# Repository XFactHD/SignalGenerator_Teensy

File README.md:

# SignalGenerator_Teensy
 Teensy 4.0 based 1MSPS Signal Generator

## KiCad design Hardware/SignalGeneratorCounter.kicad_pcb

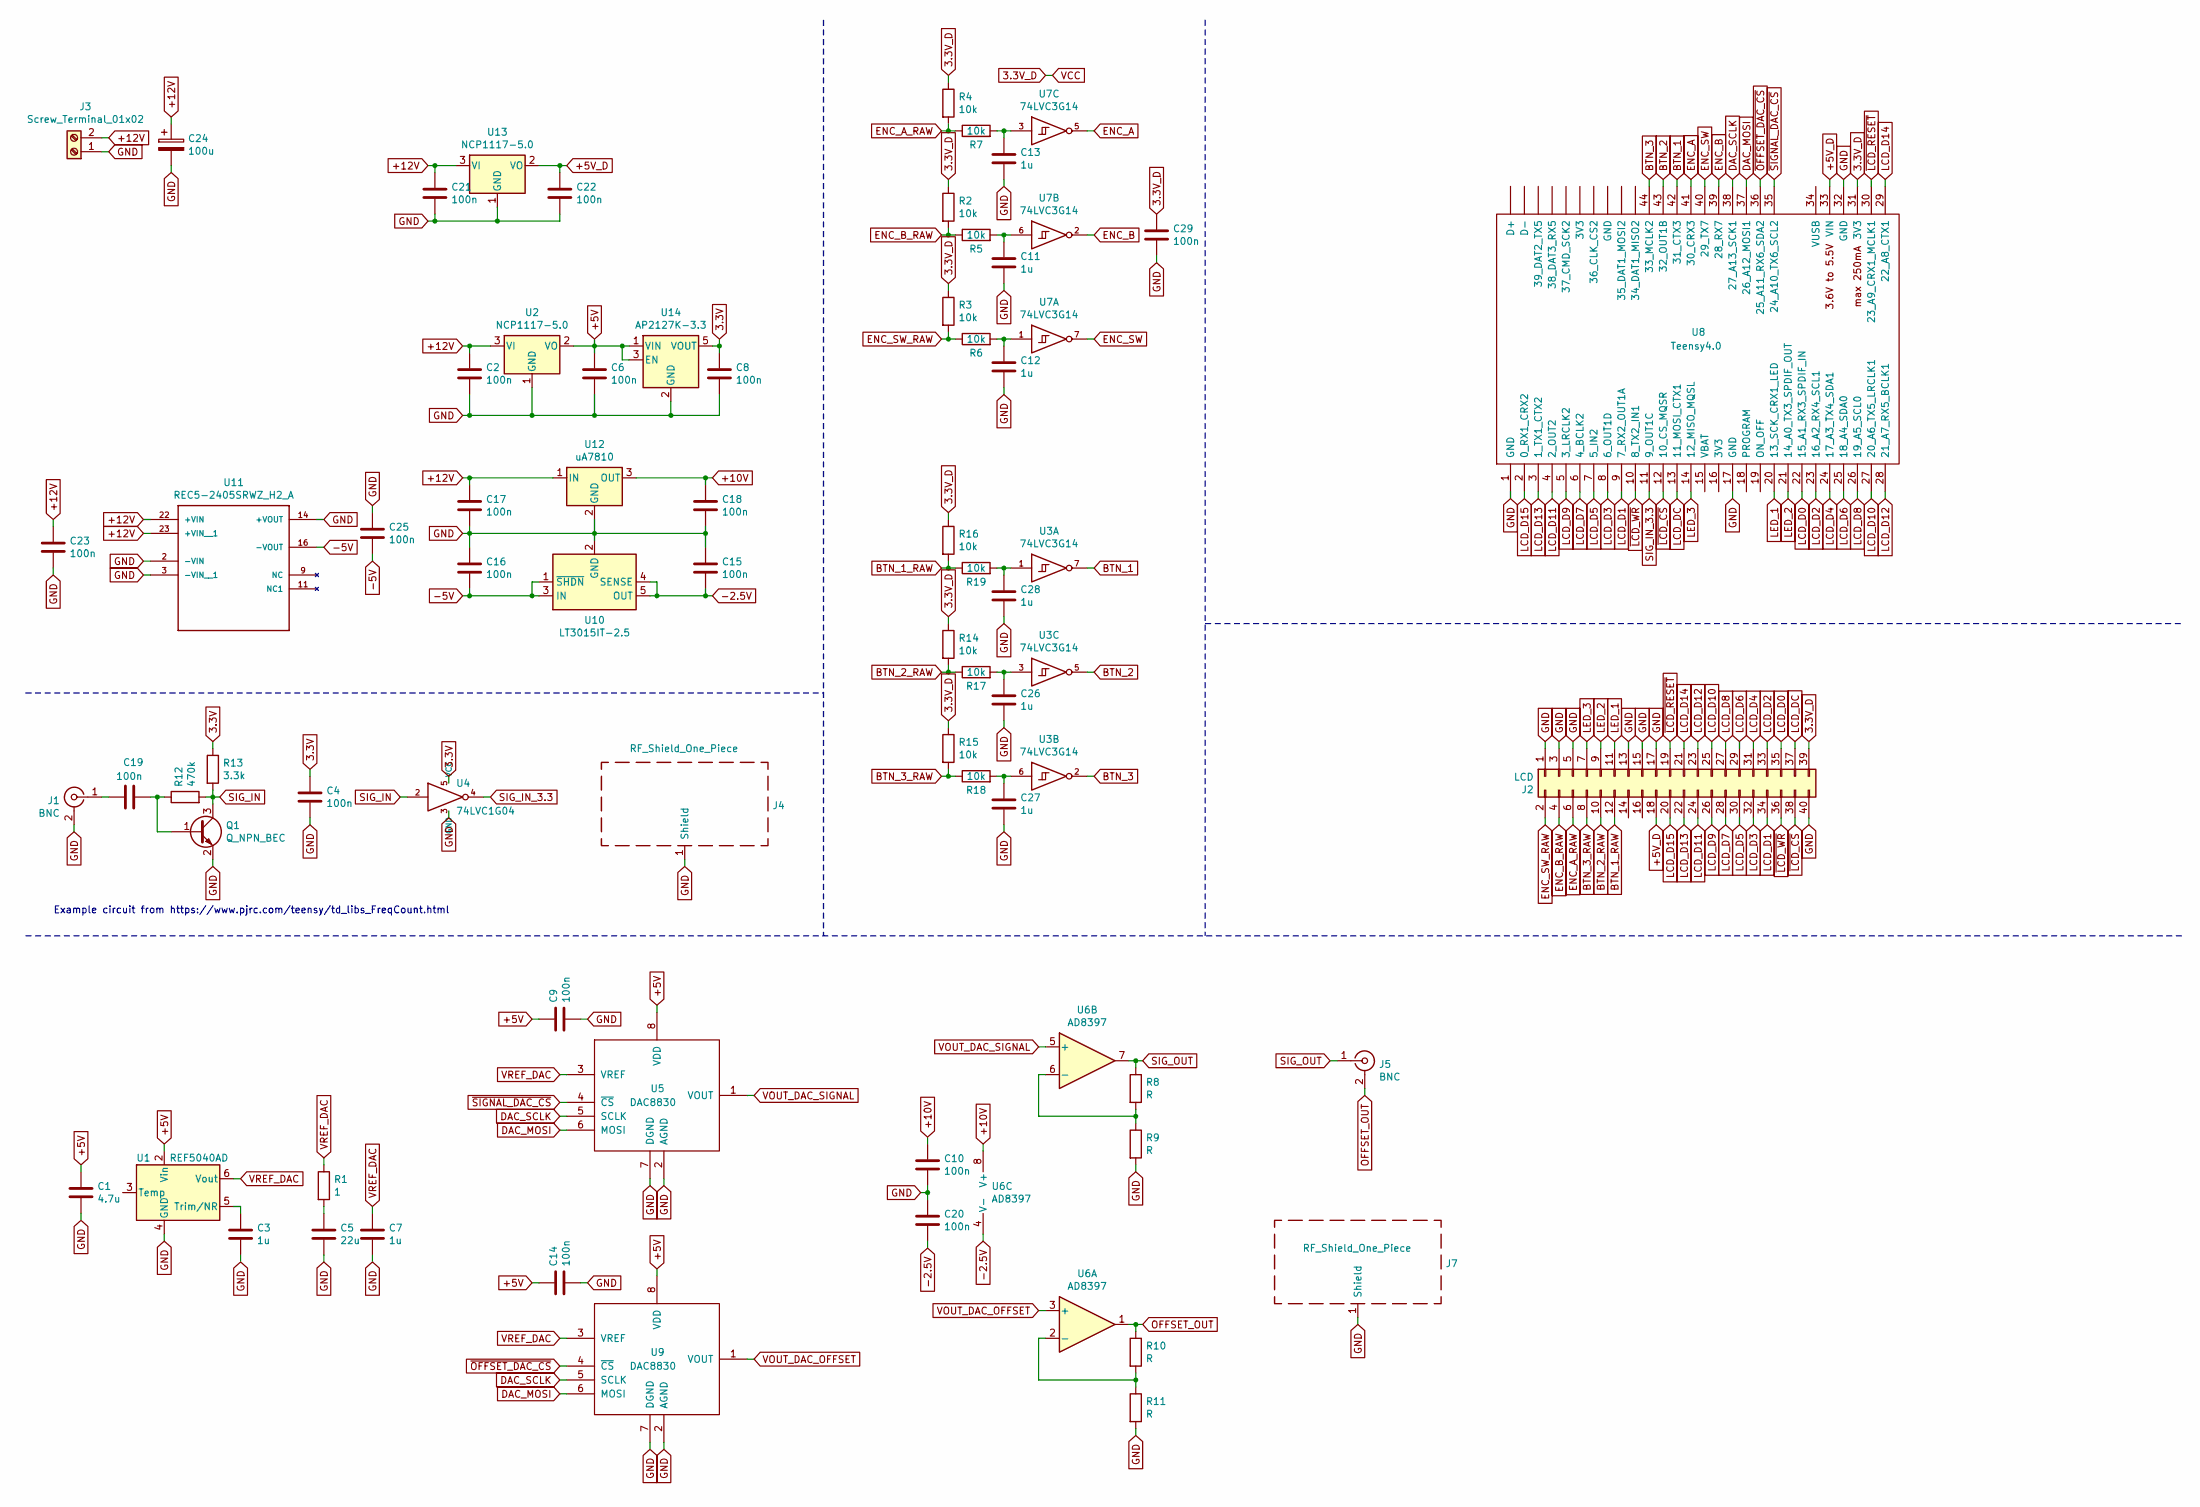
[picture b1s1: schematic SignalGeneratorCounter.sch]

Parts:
C1: 4.7u; C_0805
C2, C4, C6, C8, C9, C10, C14, C15, C16, C17, C18, C19, C20, C21, C22, C23, C25, C29: 100n; C_0805
C3, C7, C11, C12, C13, C26, C27, C28: 1u; C_0805
C5: 22u; C_0805
C24: 100u; CP_Tantalum_Case-C_EIA-6032-28_Reflow
J1, J5: BNC; BNC_Socket_TYCO-AMP
J2: LCD; HARTING_15210402601000
J3: Screw_Terminal_01x02; PhoenixContact_MSTBVA-G_02x5.08mm_Vertical
J4: RF_Shield_One_Piece; Laird_Technologies_BMI-S-201-F_13.66x12.70mm
J7: RF_Shield_One_Piece; Laird_Technologies_BMI-S-209-F_29.36x18.50mm
Q1: Q_NPN_BEC; SOT-23
R1: 1; R_0805
R2, R3, R4, R5, R6, R7, R14, R15, R16, R17, R18, R19: 10k; R_0805
R8, R9, R10, R11: R; R_0805
R12: 470k; R_0805
R13: 3.3k; R_0805
U1: REF5040AD; SOIC-8_3.9x4.9mm_Pitch1.27mm
U2, U13: NCP1117-5.0; TO-252-2
U3, U7: 74LVC3G14; VSSOP-8_2.4x2.1mm_Pitch0.5mm
U4: 74LVC1G04; SOT-23-5
U5, U9: DAC8830; SOIC-8_3.9x4.9mm_Pitch1.27mm
U6: AD8397; SOIC-8-1EP_3.9x4.9mm_Pitch1.27mm
U8: Teensy4.0; Teensy40_WithSMT_NoBack_No34
U10: LT3015IT-2.5; TO-263-5_TabPin3
U11: REC5-2405SRWZ_H2_A
U12: uA7810; TO-263-3_TabPin2
U14: AP2127K-3.3; SOT-23-5

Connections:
3.3V: C4.1, C8.1, R13.1, U4.5 (VCC), U14.5 (VOUT)
3.3V_D: C29.1, J2.39, R2.1, R3.1, R4.1, R14.1, R15.1, R16.1, U3.8 (VCC), U7.8 (VCC), U8.31 (3V3)
+5V: C1.1, C6.1, C9.1, C14.1, U1.2 (Vin), U2.2 (VO), U5.8 (VDD), U9.8 (VDD), U14.1 (VIN), U14.3 (EN)
+5V_D: C22.1, J2.18, U8.33 (VIN), U13.2 (VO)
+10V: C10.1, C18.1, U6.8 (V+), U12.3 (OUT)
+12V: C2.1, C17.1, C21.1, C23.1, C24.1, J3.2, U2.3 (VI), U11.22 (+VIN), U11.23 (+VIN__1), U12.1 (IN), U13.3 (VI)
-2.5V: C15.2, C20.2, U6.4 (V-), U10.4 (SENSE), U10.5 (OUT)
-5V: C16.2, C25.2, U10.1 (~SHDN), U10.3 (IN), U11.16 (-VOUT)
BTN_1: U3.7, U8.42 (31_CTX3)
BTN_1_RAW: J2.12, R16.2, R19.1
BTN_2: U3.5, U8.43 (32_OUT1B)
BTN_2_RAW: J2.10, R14.2, R17.1
BTN_3: U3.2, U8.44 (33_MCLK2)
BTN_3_RAW: J2.8, R15.2, R18.1
DAC_MOSI: U5.6 (MOSI), U8.37 (26_A12_MOSI1), U9.6 (MOSI)
DAC_SCLK: U5.5 (SCLK), U8.38 (27_A13_SCK1), U9.5 (SCLK)
ENC_A: U7.5, U8.41 (30_CRX3)
ENC_A_RAW: J2.6, R4.2, R7.1
ENC_B: U7.2, U8.39 (28_RX7)
ENC_B_RAW: J2.4, R2.2, R5.1
ENC_SW: U7.7, U8.40 (29_TX7)
ENC_SW_RAW: J2.2, R3.2, R6.1
GND: C1.2, C2.2, C3.2, C4.2, C5.2, C6.2, C7.2, C8.2, C9.2, C10.2, C11.2, C12.2, C13.2, C14.2, C15.1, C16.1, C17.2, C18.2, C20.1, C21.2, C22.2, C23.2, C24.2, C25.1, C26.2, C27.2, C28.2, C29.2, J1.2 (Ext), J2.1, J2.3, J2.5, J2.13, J2.15, J2.17, J2.40, J3.1, J4.1, J7.1, Q1.2 (E), R9.2, R11.2, U1.4 (GND), U2.1 (GND), U3.4 (GND), U4.3 (GND), U5.2 (AGND), U5.7 (DGND), U7.4 (GND), U8.1 (GND), U8.17 (GND), U8.32 (GND), U9.2 (AGND), U9.7 (DGND), U10.2 (GND), U11.2 (-VIN), U11.3 (-VIN__1), U11.14 (+VOUT), U12.2 (GND), U13.1 (GND), U14.2 (GND)
LCD_D0: J2.35, U8.22 (15_A1_RX3_SPDIF_IN)
LCD_D1: J2.34, U8.9 (7_RX2_OUT1A)
LCD_D2: J2.33, U8.23 (16_A2_RX4_SCL1)
LCD_D3: J2.32, U8.8 (6_OUT1D)
LCD_D4: J2.31, U8.24 (17_A3_TX4_SDA1)
LCD_D5: J2.30, U8.7 (5_IN2)
LCD_D6: J2.29, U8.25 (18_A4_SDA0)
LCD_D7: J2.28, U8.6 (4_BCLK2)
LCD_D8: J2.27, U8.26 (19_A5_SCL0)
LCD_D9: J2.26, U8.5 (3_LRCLK2)
LCD_D10: J2.25, U8.27 (20_A6_TX5_LRCLK1)
LCD_D11: J2.24, U8.4 (2_OUT2)
LCD_D12: J2.23, U8.28 (21_A7_RX5_BCLK1)
LCD_D13: J2.22, U8.3 (1_TX1_CTX2)
LCD_D14: J2.21, U8.29 (22_A8_CTX1)
LCD_D15: J2.20, U8.2 (0_RX1_CRX2)
LCD_DC: J2.37, U8.13 (11_MOSI_CTX1)
LED_1: J2.11, U8.20 (13_SCK_CRX1_LED)
LED_2: J2.9, U8.21 (14_A0_TX3_SPDIF_OUT)
LED_3: J2.7, U8.14 (12_MISO_MQSL)
unnamed: C3.1, U1.5 (Trim/NR)
unnamed: C5.1, R1.2
unnamed: C11.1, R5.2, U7.6
unnamed: C12.1, R6.2, U7.1
unnamed: C13.1, R7.2, U7.3
unnamed: C19.1, Q1.1 (B), R12.1
unnamed: C19.2, J1.1 (In)
unnamed: C26.1, R17.2, U3.3
unnamed: C27.1, R18.2, U3.6
unnamed: C28.1, R19.2, U3.1
unnamed: R8.2, R9.1, U6.6 (-)
unnamed: R10.2, R11.1, U6.2 (-)
OFFSET_OUT: J5.2 (Ext), R10.1, U6.1
SIG_IN: Q1.3 (C), R12.2, R13.2, U4.2
SIG_IN_3.3: U4.4, U8.11 (9_OUT1C)
SIG_OUT: J5.1 (In), R8.1, U6.7
VOUT_DAC_OFFSET: U6.3 (+), U9.1 (VOUT)
VOUT_DAC_SIGNAL: U5.1 (VOUT), U6.5 (+)
VREF_DAC: C7.1, R1.1, U1.6 (Vout), U5.3 (VREF), U9.3 (VREF)
~LCD_CS: J2.38, U8.12 (10_CS_MQSR)
~LCD_RESET: J2.19, U8.30 (23_A9_CRX1_MCLK1)
~LCD_WR: J2.36, U8.10 (8_TX2_IN1)
~OFFSET_DAC_CS: U8.36 (25_A11_RX6_SDA2), U9.4 (~CS)
~SIGNAL_DAC_CS: U5.4 (~CS), U8.35 (24_A10_TX6_SCL2)

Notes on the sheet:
Example circuit from https://www.pjrc.com/teensy/td_libs_FreqCount.html

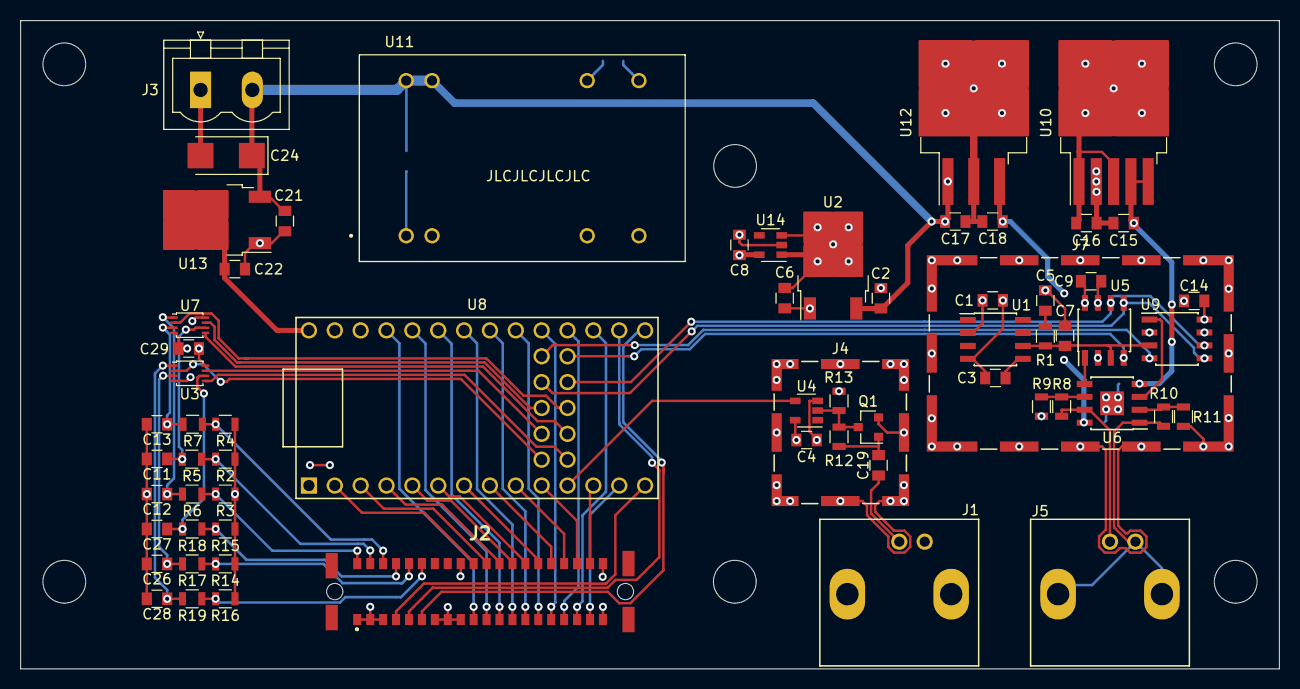
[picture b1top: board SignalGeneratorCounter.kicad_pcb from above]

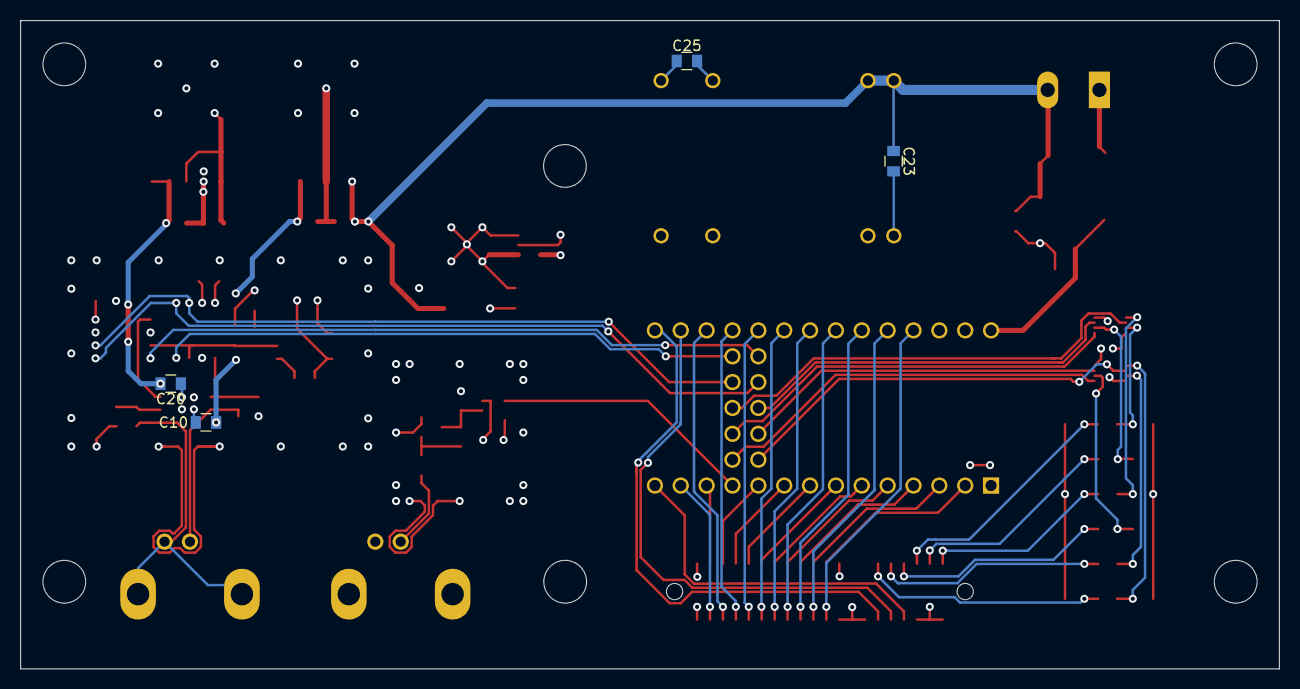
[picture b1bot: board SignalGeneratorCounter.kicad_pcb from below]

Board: 4 copper layers, 123.6 x 63.7 mm, 69 parts (4 on the bottom side), 67 nets.

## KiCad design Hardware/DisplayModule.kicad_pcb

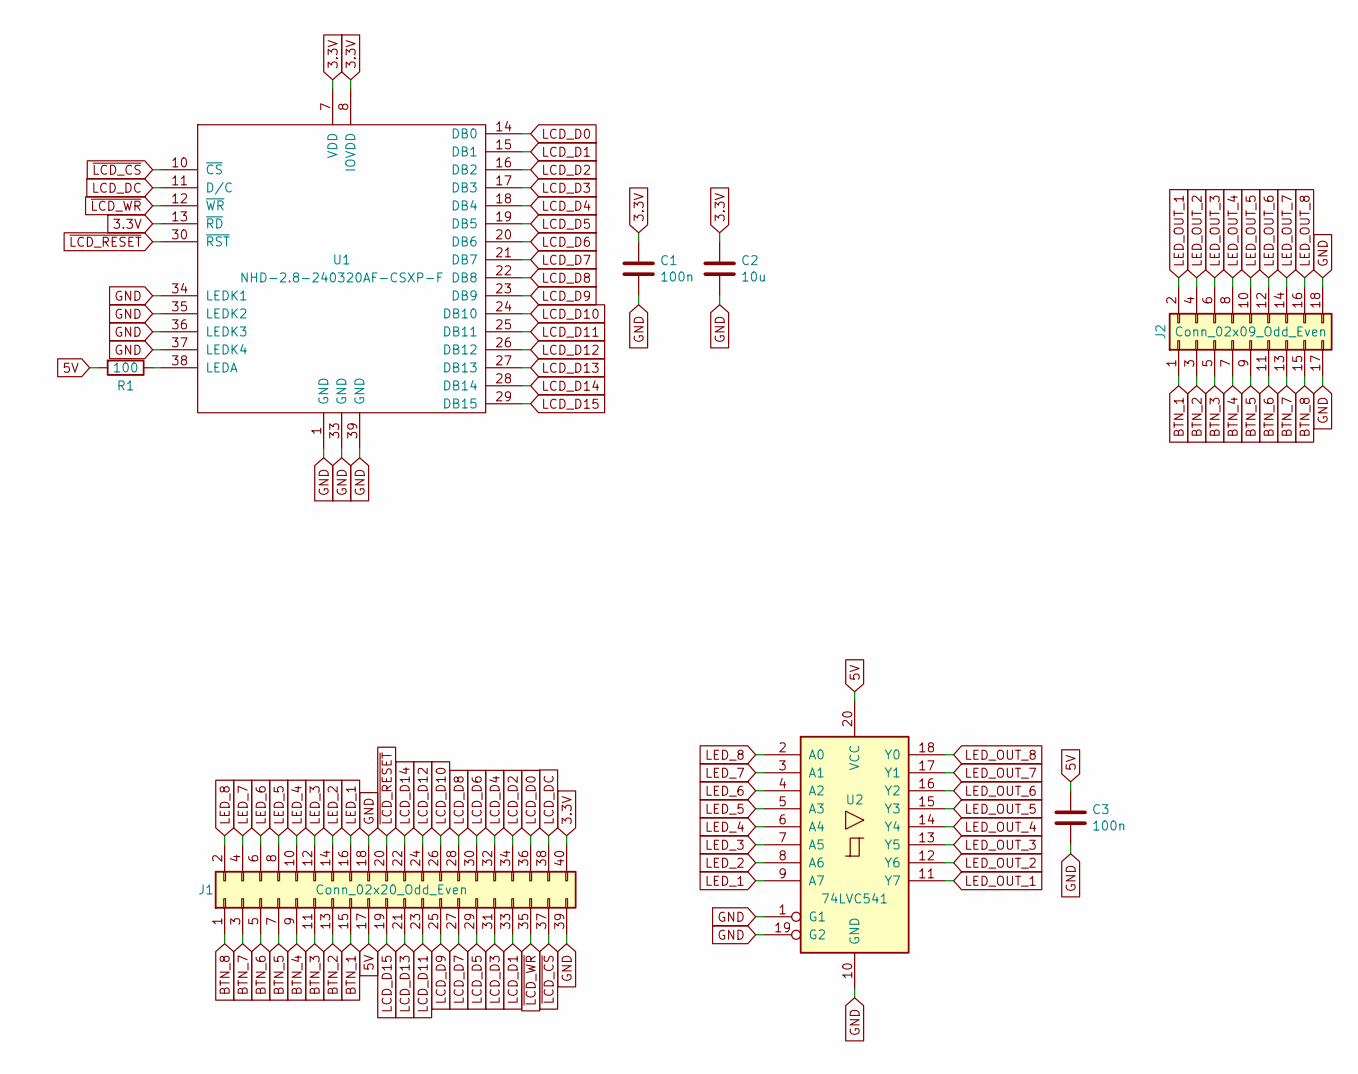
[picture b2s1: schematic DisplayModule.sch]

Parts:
C1, C3: 100n; C_0805
C2: 10u; C_0805
J1: Conn_02x20_Odd_Even; HARTING_15150402601000
J2: Conn_02x09_Odd_Even; Hirose_DF11GZ-18DP-2V20
R1: 100; R_0805
U1: NHD-2.8-240320AF-CSXP-F
U2: 74LVC541; TSSOP-20_4.4x6.5mm_Pitch0.65mm

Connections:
3.3V: C1.1, C2.1, J1.40, U1.7 (VDD), U1.8 (IOVDD), U1.13 (~RD)
5V: C3.1, J1.17, R1.2, U2.20 (VCC)
BTN_1: J1.15, J2.1
BTN_2: J1.13, J2.3
BTN_3: J1.11, J2.5
BTN_4: J1.9, J2.7
BTN_5: J1.7, J2.9
BTN_6: J1.5, J2.11
BTN_7: J1.3, J2.13
BTN_8: J1.1, J2.15
GND: C1.2, C2.2, C3.2, J1.18, J1.39, J2.17, J2.18, U1.1 (GND), U1.33 (GND), U1.34 (LEDK1), U1.35 (LEDK2), U1.36 (LEDK3), U1.37 (LEDK4), U1.39 (GND), U2.1 (G1), U2.10 (GND), U2.19 (G2)
LCD_D0: J1.36, U1.14 (DB0)
LCD_D1: J1.33, U1.15 (DB1)
LCD_D2: J1.34, U1.16 (DB2)
LCD_D3: J1.31, U1.17 (DB3)
LCD_D4: J1.32, U1.18 (DB4)
LCD_D5: J1.29, U1.19 (DB5)
LCD_D6: J1.30, U1.20 (DB6)
LCD_D7: J1.27, U1.21 (DB7)
LCD_D8: J1.28, U1.22 (DB8)
LCD_D9: J1.25, U1.23 (DB9)
LCD_D10: J1.26, U1.24 (DB10)
LCD_D11: J1.23, U1.25 (DB11)
LCD_D12: J1.24, U1.26 (DB12)
LCD_D13: J1.21, U1.27 (DB13)
LCD_D14: J1.22, U1.28 (DB14)
LCD_D15: J1.19, U1.29 (DB15)
LCD_DC: J1.38, U1.11 (D/C)
LED_1: J1.16, U2.9 (A7)
LED_2: J1.14, U2.8 (A6)
LED_3: J1.12, U2.7 (A5)
LED_4: J1.10, U2.6 (A4)
LED_5: J1.8, U2.5 (A3)
LED_6: J1.6, U2.4 (A2)
LED_7: J1.4, U2.3 (A1)
LED_8: J1.2, U2.2 (A0)
LED_OUT_1: J2.2, U2.11 (Y7)
LED_OUT_2: J2.4, U2.12 (Y6)
LED_OUT_3: J2.6, U2.13 (Y5)
LED_OUT_4: J2.8, U2.14 (Y4)
LED_OUT_5: J2.10, U2.15 (Y3)
LED_OUT_6: J2.12, U2.16 (Y2)
LED_OUT_7: J2.14, U2.17 (Y1)
LED_OUT_8: J2.16, U2.18 (Y0)
unnamed: R1.1, U1.38 (LEDA)
~LCD_CS: J1.37, U1.10 (~CS)
~LCD_RESET: J1.20, U1.30 (~RST)
~LCD_WR: J1.35, U1.12 (~WR)

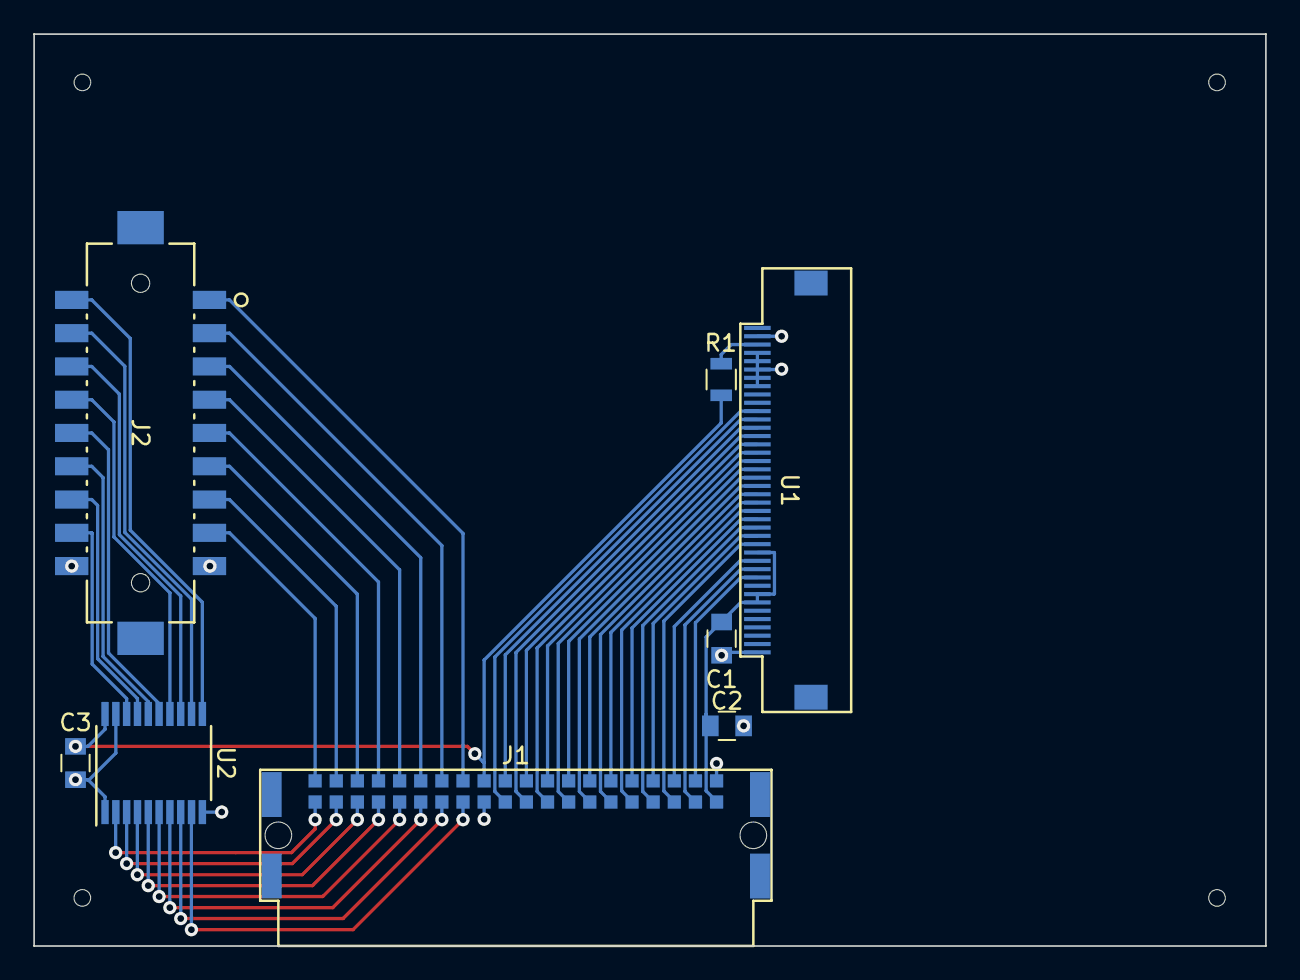
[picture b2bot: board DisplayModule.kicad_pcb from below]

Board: 2 copper layers, 74.0 x 54.8 mm, 8 parts (7 on the bottom side), 48 nets.

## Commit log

2020-12-18 Initial commit with hardware
2020-12-18 Add firmware

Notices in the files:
parts and their libraries:
Copyright 2016 Accelerated Designs. All rights reserved.
